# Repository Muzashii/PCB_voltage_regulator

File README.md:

# PCB_voltage_regulator
PBC of a voltage regulator done on a college assignment

# Imagens

Schematic of the project : 

Schematic of the PCB : 

Top layer of 3D PCB : 

## Installation

##### Use KiCad to open the project file

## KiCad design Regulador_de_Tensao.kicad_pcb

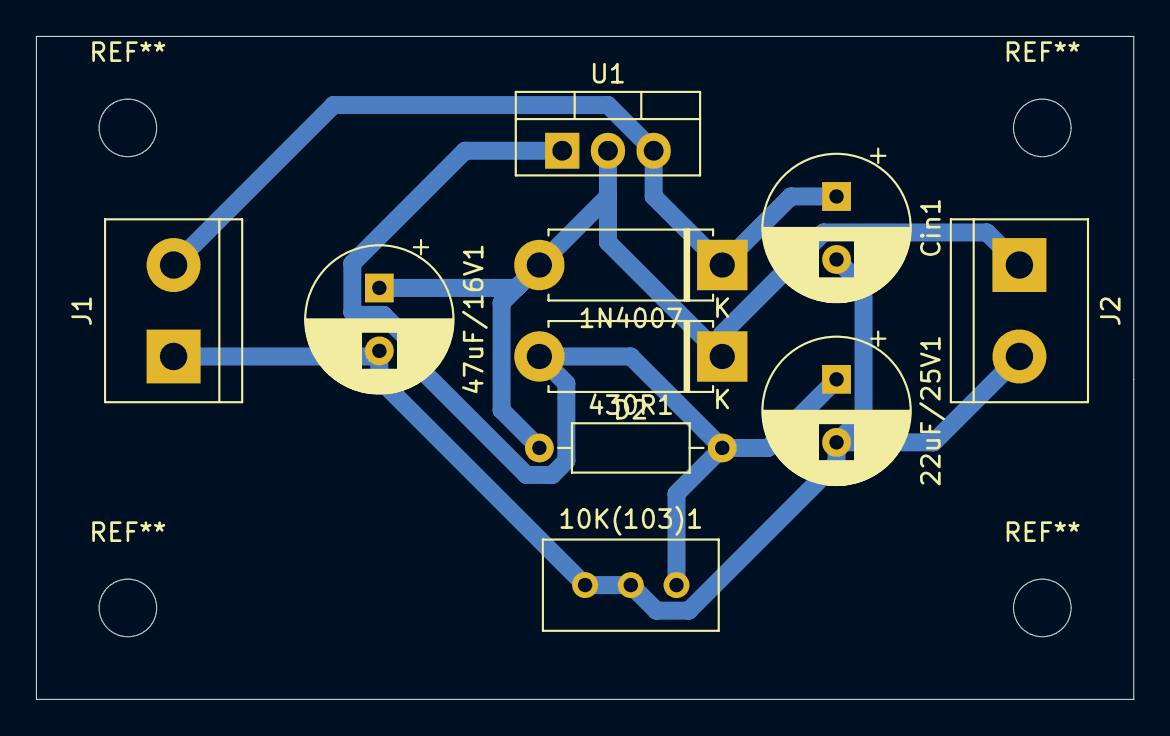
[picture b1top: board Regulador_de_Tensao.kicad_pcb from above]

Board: 2 copper layers, 61.0 x 36.8 mm, 10 parts (0 on the bottom side), 4 nets.

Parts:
1N4007: D1; D_5W_P10.16mm_Horizontal
10K(103)1: R_POT; Potentiometer_Bourns_3296W_Vertical
22uF/25V1: Cadj; CP_Radial_D8.0mm_P3.50mm
47uF/16V1: Co; CP_Radial_D8.0mm_P3.50mm
430R1: R1; R_Axial_DIN0207_L6.3mm_D2.5mm_P10.16mm_Horizontal
Cin1: 100uF/50V; CP_Radial_D8.0mm_P3.50mm
D2: 1N4007; D_5W_P10.16mm_Horizontal
J1, J2: Screw_Terminal_01x02; TerminalBlock_bornier-2_P5.08mm
U1: LM317; TO-220-3_Vertical

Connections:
unnamed: 1N4007.1, Cin1.1, J1.2, U1.3
unnamed: 1N4007.2, 47uF/16V1.1, 430R1.1, D2.1, J2.1, U1.2
unnamed: 10K(103)1.1, 22uF/25V1.1, 430R1.2, D2.2, U1.1
unnamed: 10K(103)1.2, 10K(103)1.3, 22uF/25V1.2, 47uF/16V1.2, Cin1.2, J1.1, J2.2

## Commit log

2021-05-31 finished project
2021-05-31 PCB Final
